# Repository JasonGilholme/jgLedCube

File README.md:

## jgLedCube

Open source software and hardware for creating an LED Cube.

### Software

The available code is intended to an SDK to allow people to make their cubes do more things as well as interact with other devices. 

The two main components of this are:

* core.cpp - intended for the cube micro controller and handles the data arrays for the cube.  It's implementation matches the provided hardware as well.
* serial.cpp - provides a standardized interface for communicating with an LED cube.  This provides higher level functions like set_led(), clear() etc to be used from Android Apps, Desktop programs and other micro controllers.

### Hardware

The hardware consists of two modular boards which are daisy chained together.  

The "column control board" acts as a base for the cube and provides 8 columns in a 4x2 arrangement.  This can be used to make arbitrary sized cubes, and shapes that aren't cubes too!

The "level control board" is used for multiplexing the different horizontal layers in the cube. It should be connected after all the column control boards.

A main controller and power solution is not provided as the requirements may vary depending on your exact product.  There are test programs for Arduino included, but it should also be possible to compile the core libs for other devices. STM32 etc.

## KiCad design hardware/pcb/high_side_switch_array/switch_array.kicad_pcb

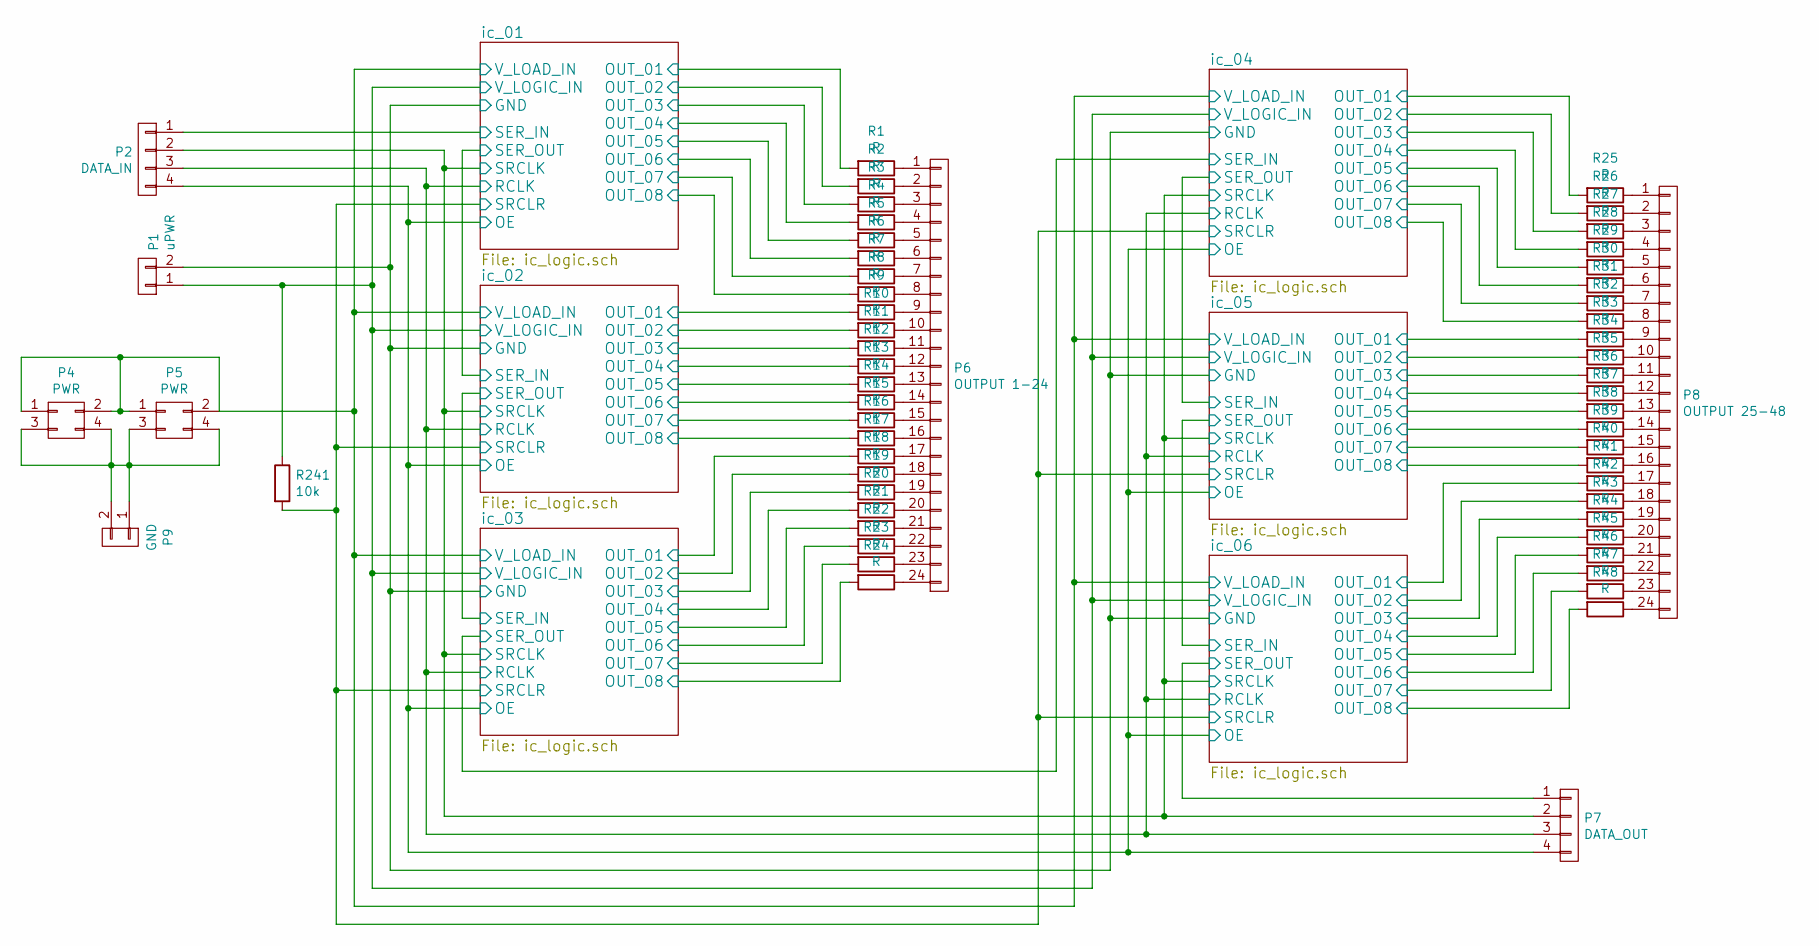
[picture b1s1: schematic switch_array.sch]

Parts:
P1: uPWR; Socket_Strip_Straight_1x02
P2: DATA_IN; Socket_Strip_Straight_1x04
P4, P5: PWR; Socket_Strip_Straight_2x02
P6: OUTPUT 1-24; Socket_Strip_Straight_2x12
P7: DATA_OUT; Socket_Strip_Straight_1x04
P8: OUTPUT 25-48; Socket_Strip_Straight_2x12
P9: GND; Socket_Strip_Straight_1x02
R1, R2, R3, R4, R5, R6, R7, R8, R9, R10, R11, R12, R13, R14, R15, R16, R17, R18, R19, R20, R21, R22, R23, R24, R25, R26, R27, R28, R29, R30, R31, R32, R33, R34, R35, R36, R37, R38, R39, R40, R41, R42, R43, R44, R45, R46, R47, R48: R; R_1206_HandSoldering
R241: 10k; R_1206_HandSoldering_NOREF

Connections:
/ic_01/OE: P2.4, P7.4; also elsewhere on the board
/ic_01/OUT_01: R1.2; also elsewhere on the board
/ic_01/OUT_02: R2.2; also elsewhere on the board
/ic_01/OUT_03: R3.2; also elsewhere on the board
/ic_01/OUT_04: R4.2; also elsewhere on the board
/ic_01/OUT_05: R5.2; also elsewhere on the board
/ic_01/OUT_06: R6.2; also elsewhere on the board
/ic_01/OUT_07: R7.2; also elsewhere on the board
/ic_01/OUT_08: R8.2; also elsewhere on the board
/ic_01/RCLK: P2.3, P7.3; also elsewhere on the board
/ic_01/SER_IN: P2.1; also elsewhere on the board
/ic_01/SRCLK: P2.2, P7.2; also elsewhere on the board
/ic_01/SRCLR: R241.2; also elsewhere on the board
/ic_01/V_LOAD_IN: P4.1, P4.2, P5.1, P5.2; also elsewhere on the board
/ic_02/OUT_01: R9.2; also elsewhere on the board
/ic_02/OUT_02: R10.2; also elsewhere on the board
/ic_02/OUT_03: R11.2; also elsewhere on the board
/ic_02/OUT_04: R12.2; also elsewhere on the board
/ic_02/OUT_05: R13.2; also elsewhere on the board
/ic_02/OUT_06: R14.2; also elsewhere on the board
/ic_02/OUT_07: R15.2; also elsewhere on the board
/ic_02/OUT_08: R16.2; also elsewhere on the board
/ic_03/OUT_01: R17.2; also elsewhere on the board
/ic_03/OUT_02: R18.2; also elsewhere on the board
/ic_03/OUT_03: R19.2; also elsewhere on the board
/ic_03/OUT_04: R20.2; also elsewhere on the board
/ic_03/OUT_05: R21.2; also elsewhere on the board
/ic_03/OUT_06: R22.2; also elsewhere on the board
/ic_03/OUT_07: R23.2; also elsewhere on the board
/ic_03/OUT_08: R24.2; also elsewhere on the board
/ic_04/OUT_01: R25.2; also elsewhere on the board
/ic_04/OUT_02: R26.2; also elsewhere on the board
/ic_04/OUT_03: R27.2; also elsewhere on the board
/ic_04/OUT_04: R28.2; also elsewhere on the board
/ic_04/OUT_05: R29.2; also elsewhere on the board
/ic_04/OUT_06: R30.2; also elsewhere on the board
/ic_04/OUT_07: R31.2; also elsewhere on the board
/ic_04/OUT_08: R32.2; also elsewhere on the board
/ic_05/OUT_01: R33.2; also elsewhere on the board
/ic_05/OUT_02: R34.2; also elsewhere on the board
/ic_05/OUT_03: R35.2; also elsewhere on the board
/ic_05/OUT_04: R36.2; also elsewhere on the board
/ic_05/OUT_05: R37.2; also elsewhere on the board
/ic_05/OUT_06: R38.2; also elsewhere on the board
/ic_05/OUT_07: R39.2; also elsewhere on the board
/ic_05/OUT_08: R40.2; also elsewhere on the board
/ic_06/OUT_01: R41.2; also elsewhere on the board
/ic_06/OUT_02: R42.2; also elsewhere on the board
/ic_06/OUT_03: R43.2; also elsewhere on the board
/ic_06/OUT_04: R44.2; also elsewhere on the board
/ic_06/OUT_05: R45.2; also elsewhere on the board
/ic_06/OUT_06: R46.2; also elsewhere on the board
/ic_06/OUT_07: R47.2; also elsewhere on the board
/ic_06/OUT_08: R48.2; also elsewhere on the board
/ic_06/SER_OUT: P7.1; also elsewhere on the board
GND: P1.2; also elsewhere on the board
unnamed: P4.3, P4.4, P5.3, P5.4, P9.1, P9.2
unnamed: P6.1, R1.1
unnamed: P6.2, R2.1
unnamed: P6.3, R3.1
unnamed: P6.4, R4.1
unnamed: P6.5, R5.1
unnamed: P6.6, R6.1
unnamed: P6.7, R7.1
unnamed: P6.8, R8.1
unnamed: P6.9, R9.1
unnamed: P6.10, R10.1
unnamed: P6.11, R11.1
unnamed: P6.12, R12.1
unnamed: P6.13, R13.1
unnamed: P6.14, R14.1
unnamed: P6.15, R15.1
unnamed: P6.16, R16.1
unnamed: P6.17, R17.1
unnamed: P6.18, R18.1
unnamed: P6.19, R19.1
unnamed: P6.20, R20.1
unnamed: P6.21, R21.1
unnamed: P6.22, R22.1
unnamed: P6.23, R23.1
unnamed: P6.24, R24.1
unnamed: P8.1, R25.1
unnamed: P8.2, R26.1
unnamed: P8.3, R27.1
unnamed: P8.4, R28.1
unnamed: P8.5, R29.1
unnamed: P8.6, R30.1
unnamed: P8.7, R31.1
unnamed: P8.8, R32.1
unnamed: P8.9, R33.1
unnamed: P8.10, R34.1
unnamed: P8.11, R35.1
unnamed: P8.12, R36.1
unnamed: P8.13, R37.1
unnamed: P8.14, R38.1
unnamed: P8.15, R39.1
unnamed: P8.16, R40.1
unnamed: P8.17, R41.1
unnamed: P8.18, R42.1
unnamed: P8.19, R43.1
unnamed: P8.20, R44.1
unnamed: P8.21, R45.1
unnamed: P8.22, R46.1
unnamed: P8.23, R47.1
unnamed: P8.24, R48.1
VCC: P1.1, R241.1; also elsewhere on the board

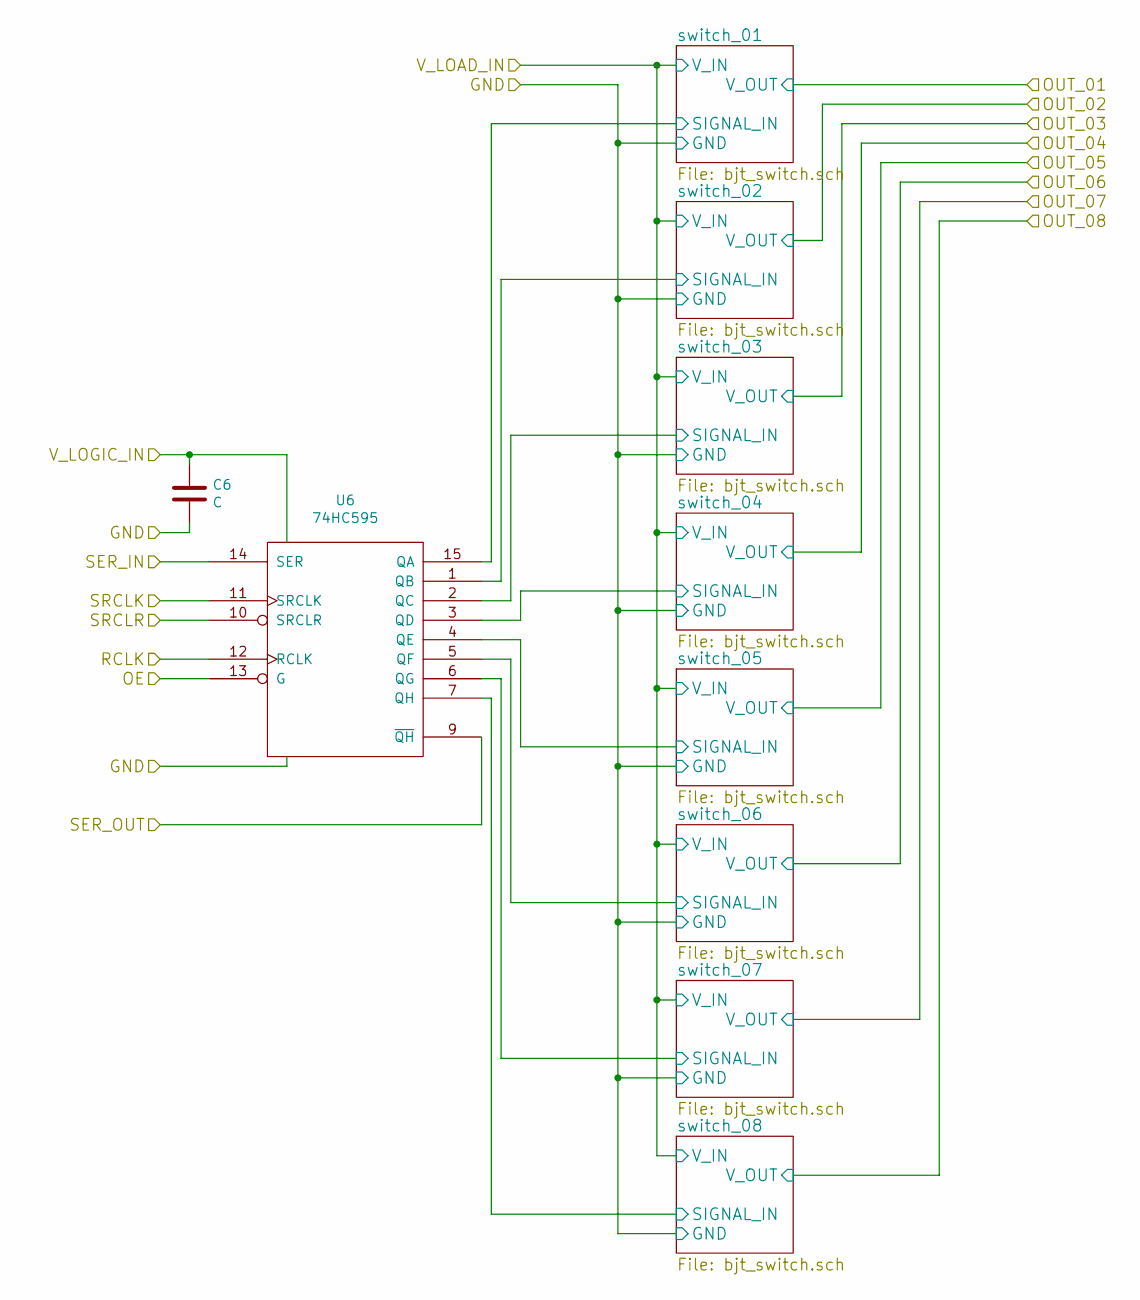
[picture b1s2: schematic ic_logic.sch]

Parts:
C1: C; C_1206_HandSoldering
U1: 74HC595; SO-16-N

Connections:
/ic_01/OE: U1.13 (G); also elsewhere on the board
/ic_01/RCLK: U1.12 (RCLK); also elsewhere on the board
/ic_01/SER_IN: U1.14 (SER); also elsewhere on the board
/ic_01/SRCLK: U1.11 (SRCLK); also elsewhere on the board
/ic_01/SRCLR: U1.10 (SRCLR); also elsewhere on the board
/ic_01/switch_01/SIGNAL_IN: U1.15 (QA); also elsewhere on the board
/ic_01/switch_02/SIGNAL_IN: U1.1 (QB); also elsewhere on the board
/ic_01/switch_03/SIGNAL_IN: U1.2 (QC); also elsewhere on the board
/ic_01/switch_04/SIGNAL_IN: U1.3 (QD); also elsewhere on the board
/ic_01/switch_05/SIGNAL_IN: U1.4 (QE); also elsewhere on the board
/ic_01/switch_06/SIGNAL_IN: U1.5 (QF); also elsewhere on the board
/ic_01/switch_07/SIGNAL_IN: U1.6 (QG); also elsewhere on the board
/ic_01/switch_08/SIGNAL_IN: U1.7 (QH); also elsewhere on the board
/ic_02/SER_IN: U1.9 (~QH); also elsewhere on the board
GND: C1.2, U1.8 (GND); also elsewhere on the board
VCC: C1.1, U1.16 (VCC); also elsewhere on the board

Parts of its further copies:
C2, C3, C4, C5, C6: C; C_1206_HandSoldering
U2, U3, U4, U5, U6: 74HC595; SO-16-N

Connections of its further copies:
/ic_01/OE: U2.13 (G), U3.13 (G), U4.13 (G), U5.13 (G), U6.13 (G); also elsewhere on the board
/ic_01/RCLK: U2.12 (RCLK), U3.12 (RCLK), U4.12 (RCLK), U5.12 (RCLK), U6.12 (RCLK); also elsewhere on the board
/ic_01/SRCLK: U2.11 (SRCLK), U3.11 (SRCLK), U4.11 (SRCLK), U5.11 (SRCLK), U6.11 (SRCLK); also elsewhere on the board
/ic_01/SRCLR: U2.10 (SRCLR), U3.10 (SRCLR), U4.10 (SRCLR), U5.10 (SRCLR), U6.10 (SRCLR); also elsewhere on the board
/ic_02/SER_IN: U2.14 (SER); also elsewhere on the board
/ic_02/switch_01/SIGNAL_IN: U2.15 (QA); also elsewhere on the board
/ic_02/switch_02/SIGNAL_IN: U2.1 (QB); also elsewhere on the board
/ic_02/switch_03/SIGNAL_IN: U2.2 (QC); also elsewhere on the board
/ic_02/switch_04/SIGNAL_IN: U2.3 (QD); also elsewhere on the board
/ic_02/switch_05/SIGNAL_IN: U2.4 (QE); also elsewhere on the board
/ic_02/switch_06/SIGNAL_IN: U2.5 (QF); also elsewhere on the board
/ic_02/switch_07/SIGNAL_IN: U2.6 (QG); also elsewhere on the board
/ic_02/switch_08/SIGNAL_IN: U2.7 (QH); also elsewhere on the board
/ic_03/SER_IN: U2.9 (~QH), U3.14 (SER)
/ic_03/switch_01/SIGNAL_IN: U3.15 (QA); also elsewhere on the board
/ic_03/switch_02/SIGNAL_IN: U3.1 (QB); also elsewhere on the board
/ic_03/switch_03/SIGNAL_IN: U3.2 (QC); also elsewhere on the board
/ic_03/switch_04/SIGNAL_IN: U3.3 (QD); also elsewhere on the board
/ic_03/switch_05/SIGNAL_IN: U3.4 (QE); also elsewhere on the board
/ic_03/switch_06/SIGNAL_IN: U3.5 (QF); also elsewhere on the board
/ic_03/switch_07/SIGNAL_IN: U3.6 (QG); also elsewhere on the board
/ic_03/switch_08/SIGNAL_IN: U3.7 (QH); also elsewhere on the board
/ic_04/SER_IN: U3.9 (~QH), U4.14 (SER)
/ic_04/switch_01/SIGNAL_IN: U4.15 (QA); also elsewhere on the board
/ic_04/switch_02/SIGNAL_IN: U4.1 (QB); also elsewhere on the board
/ic_04/switch_03/SIGNAL_IN: U4.2 (QC); also elsewhere on the board
/ic_04/switch_04/SIGNAL_IN: U4.3 (QD); also elsewhere on the board
/ic_04/switch_05/SIGNAL_IN: U4.4 (QE); also elsewhere on the board
/ic_04/switch_06/SIGNAL_IN: U4.5 (QF); also elsewhere on the board
/ic_04/switch_07/SIGNAL_IN: U4.6 (QG); also elsewhere on the board
/ic_04/switch_08/SIGNAL_IN: U4.7 (QH); also elsewhere on the board
/ic_05/SER_IN: U4.9 (~QH), U5.14 (SER)
/ic_05/switch_01/SIGNAL_IN: U5.15 (QA); also elsewhere on the board
/ic_05/switch_02/SIGNAL_IN: U5.1 (QB); also elsewhere on the board
/ic_05/switch_03/SIGNAL_IN: U5.2 (QC); also elsewhere on the board
/ic_05/switch_04/SIGNAL_IN: U5.3 (QD); also elsewhere on the board
/ic_05/switch_05/SIGNAL_IN: U5.4 (QE); also elsewhere on the board
/ic_05/switch_06/SIGNAL_IN: U5.5 (QF); also elsewhere on the board
/ic_05/switch_07/SIGNAL_IN: U5.6 (QG); also elsewhere on the board
/ic_05/switch_08/SIGNAL_IN: U5.7 (QH); also elsewhere on the board
/ic_06/SER_IN: U5.9 (~QH), U6.14 (SER)
/ic_06/SER_OUT: U6.9 (~QH); also elsewhere on the board
/ic_06/switch_01/SIGNAL_IN: U6.15 (QA); also elsewhere on the board
/ic_06/switch_02/SIGNAL_IN: U6.1 (QB); also elsewhere on the board
/ic_06/switch_03/SIGNAL_IN: U6.2 (QC); also elsewhere on the board
/ic_06/switch_04/SIGNAL_IN: U6.3 (QD); also elsewhere on the board
/ic_06/switch_05/SIGNAL_IN: U6.4 (QE); also elsewhere on the board
/ic_06/switch_06/SIGNAL_IN: U6.5 (QF); also elsewhere on the board
/ic_06/switch_07/SIGNAL_IN: U6.6 (QG); also elsewhere on the board
/ic_06/switch_08/SIGNAL_IN: U6.7 (QH); also elsewhere on the board
GND: C2.2, C3.2, C4.2, C5.2, C6.2, U2.8 (GND), U3.8 (GND), U4.8 (GND), U5.8 (GND), U6.8 (GND); also elsewhere on the board
VCC: C2.1, C3.1, C4.1, C5.1, C6.1, U2.16 (VCC), U3.16 (VCC), U4.16 (VCC), U5.16 (VCC), U6.16 (VCC); also elsewhere on the board

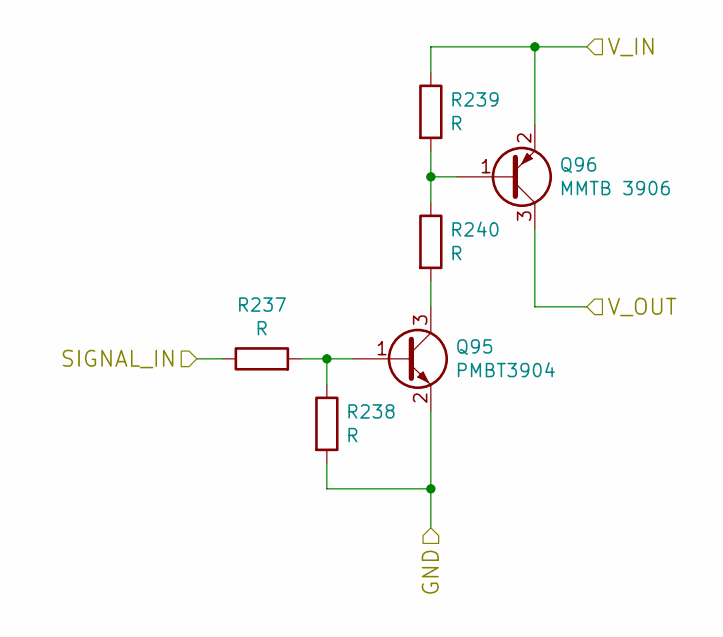
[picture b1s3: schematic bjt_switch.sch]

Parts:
Q1: PMBT3904; SOT-23
Q2: MMTB 3906; SOT-23
R49, R50, R51, R52: R; R_1206_HandSoldering

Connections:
/ic_01/OUT_02: Q2.3 (C); also elsewhere on the board
/ic_01/V_LOAD_IN: Q2.2 (E), R51.1; also elsewhere on the board
/ic_01/switch_02/SIGNAL_IN: R49.1; also elsewhere on the board
GND: Q1.2 (E), R50.2; also elsewhere on the board
unnamed: Q1.1 (B), R49.2, R50.1
unnamed: Q1.3 (C), R52.2
unnamed: Q2.1 (B), R51.2, R52.1

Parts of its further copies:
Q3, Q5, Q7, Q9, Q11, Q13, Q15, Q17, Q19, Q21, Q23, Q25, Q27, Q29, Q31, Q33, Q35, Q37, Q39, Q41, Q43, Q45, Q47, Q49, Q51, Q53, Q55, Q57, Q59, Q61, Q63, Q65, Q67, Q69, Q71, Q73, Q75, Q77, Q79, Q81, Q83, Q85, Q87, Q89, Q91, Q93, Q95: PMBT3904; SOT-23
Q4, Q6, Q8, Q10, Q12, Q14, Q16, Q18, Q20, Q22, Q24, Q26, Q28, Q30, Q32, Q34, Q36, Q38, Q40, Q42, Q44, Q46, Q48, Q50, Q52, Q54, Q56, Q58, Q60, Q62, Q64, Q66, Q68, Q70, Q72, Q74, Q76, Q78, Q80, Q82, Q84, Q86, Q88, Q90, Q92, Q94, Q96: MMTB 3906; SOT-23
R53, R54, R55, R56, R57, R58, R59, R60, R61, R62, R63, R64, R65, R66, R67, R68, R69, R70, R71, R72, R73, R74, R75, R76, R77, R78, R79, R80, R81, R82, R83, R84, R85, R86, R87, R88, R89, R90, R91, R92, R93, R94, R95, R96, R97, R98, R99, R100, R101, R102, R103, R104, R105, R106, R107, R108, R109, R110, R111, R112, R113, R114, R115, R116, R117, R118, R119, R120, R121, R122, R123, R124, R125, R126, R127, R128, R129, R130, R131, R132, R133, R134, R135, R136, R137, R138, R139, R140, R141, R142, R143, R144, R145, R146, R147, R148, R149, R150, R151, R152, R153, R154, R155, R156, R157, R158, R159, R160, R161, R162, R163, R164, R165, R166, R167, R168, R169, R170, R171, R172, R173, R174, R175, R176, R177, R178, R179, R180, R181, R182, R183, R184, R185, R186, R187, R188, R189, R190, R191, R192, R193, R194, R195, R196, R197, R198, R199, R200, R201, R202, R203, R204, R205, R206, R207, R208, R209, R210, R211, R212, R213, R214, R215, R216, R217, R218, R219, R220, R221, R222, R223, R224, R225, R226, R227, R228, R229, R230, R231, R232, R233, R234, R235, R236, R237, R238, R239, R240: R; R_1206_HandSoldering

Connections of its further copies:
/ic_01/OUT_01: Q16.3 (C); also elsewhere on the board
/ic_01/OUT_03: Q4.3 (C); also elsewhere on the board
/ic_01/OUT_04: Q6.3 (C); also elsewhere on the board
/ic_01/OUT_05: Q8.3 (C); also elsewhere on the board
/ic_01/OUT_06: Q10.3 (C); also elsewhere on the board
/ic_01/OUT_07: Q12.3 (C); also elsewhere on the board
/ic_01/OUT_08: Q14.3 (C); also elsewhere on the board
/ic_01/V_LOAD_IN: Q4.2 (E), Q6.2 (E), Q8.2 (E), Q10.2 (E), Q12.2 (E), Q14.2 (E), Q16.2 (E), Q18.2 (E), Q20.2 (E), Q22.2 (E), Q24.2 (E), Q26.2 (E), Q28.2 (E), Q30.2 (E), Q32.2 (E), Q34.2 (E), Q36.2 (E), Q38.2 (E), Q40.2 (E), Q42.2 (E), Q44.2 (E), Q46.2 (E), Q48.2 (E), Q50.2 (E), Q52.2 (E), Q54.2 (E), Q56.2 (E), Q58.2 (E), Q60.2 (E), Q62.2 (E), Q64.2 (E), Q66.2 (E), Q68.2 (E), Q70.2 (E), Q72.2 (E), Q74.2 (E), Q76.2 (E), Q78.2 (E), Q80.2 (E), Q82.2 (E), Q84.2 (E), Q86.2 (E), Q88.2 (E), Q90.2 (E), Q92.2 (E), Q94.2 (E), Q96.2 (E), R55.1, R59.1, R63.1, R67.1, R71.1, R75.1, R79.1, R83.1, R87.1, R91.1, R95.1, R99.1, R103.1, R107.1, R111.1, R115.1, R119.1, R123.1, R127.1, R131.1, R135.1, R139.1, R143.1, R147.1, R151.1, R155.1, R159.1, R163.1, R167.1, R171.1, R175.1, R179.1, R183.1, R187.1, R191.1, R195.1, R199.1, R203.1, R207.1, R211.1, R215.1, R219.1, R223.1, R227.1, R231.1, R235.1, R239.1; also elsewhere on the board
/ic_01/switch_01/SIGNAL_IN: R77.1; also elsewhere on the board
/ic_01/switch_03/SIGNAL_IN: R53.1; also elsewhere on the board
/ic_01/switch_04/SIGNAL_IN: R57.1; also elsewhere on the board
/ic_01/switch_05/SIGNAL_IN: R61.1; also elsewhere on the board
/ic_01/switch_06/SIGNAL_IN: R65.1; also elsewhere on the board
/ic_01/switch_07/SIGNAL_IN: R69.1; also elsewhere on the board
/ic_01/switch_08/SIGNAL_IN: R73.1; also elsewhere on the board
/ic_02/OUT_01: Q32.3 (C); also elsewhere on the board
/ic_02/OUT_02: Q18.3 (C); also elsewhere on the board
/ic_02/OUT_03: Q20.3 (C); also elsewhere on the board
/ic_02/OUT_04: Q22.3 (C); also elsewhere on the board
/ic_02/OUT_05: Q24.3 (C); also elsewhere on the board
/ic_02/OUT_06: Q26.3 (C); also elsewhere on the board
/ic_02/OUT_07: Q28.3 (C); also elsewhere on the board
/ic_02/OUT_08: Q30.3 (C); also elsewhere on the board
/ic_02/switch_01/SIGNAL_IN: R109.1; also elsewhere on the board
/ic_02/switch_02/SIGNAL_IN: R81.1; also elsewhere on the board
/ic_02/switch_03/SIGNAL_IN: R85.1; also elsewhere on the board
/ic_02/switch_04/SIGNAL_IN: R89.1; also elsewhere on the board
/ic_02/switch_05/SIGNAL_IN: R93.1; also elsewhere on the board
/ic_02/switch_06/SIGNAL_IN: R97.1; also elsewhere on the board
/ic_02/switch_07/SIGNAL_IN: R101.1; also elsewhere on the board
/ic_02/switch_08/SIGNAL_IN: R105.1; also elsewhere on the board
/ic_03/OUT_01: Q48.3 (C); also elsewhere on the board
/ic_03/OUT_02: Q34.3 (C); also elsewhere on the board
/ic_03/OUT_03: Q36.3 (C); also elsewhere on the board
/ic_03/OUT_04: Q38.3 (C); also elsewhere on the board
/ic_03/OUT_05: Q40.3 (C); also elsewhere on the board
/ic_03/OUT_06: Q42.3 (C); also elsewhere on the board
/ic_03/OUT_07: Q44.3 (C); also elsewhere on the board
/ic_03/OUT_08: Q46.3 (C); also elsewhere on the board
/ic_03/switch_01/SIGNAL_IN: R141.1; also elsewhere on the board
/ic_03/switch_02/SIGNAL_IN: R113.1; also elsewhere on the board
/ic_03/switch_03/SIGNAL_IN: R117.1; also elsewhere on the board
/ic_03/switch_04/SIGNAL_IN: R121.1; also elsewhere on the board
/ic_03/switch_05/SIGNAL_IN: R125.1; also elsewhere on the board
/ic_03/switch_06/SIGNAL_IN: R129.1; also elsewhere on the board
/ic_03/switch_07/SIGNAL_IN: R133.1; also elsewhere on the board
/ic_03/switch_08/SIGNAL_IN: R137.1; also elsewhere on the board
/ic_04/OUT_01: Q64.3 (C); also elsewhere on the board
/ic_04/OUT_02: Q50.3 (C); also elsewhere on the board
/ic_04/OUT_03: Q52.3 (C); also elsewhere on the board
/ic_04/OUT_04: Q54.3 (C); also elsewhere on the board
/ic_04/OUT_05: Q56.3 (C); also elsewhere on the board
/ic_04/OUT_06: Q58.3 (C); also elsewhere on the board
/ic_04/OUT_07: Q60.3 (C); also elsewhere on the board
/ic_04/OUT_08: Q62.3 (C); also elsewhere on the board
/ic_04/switch_01/SIGNAL_IN: R173.1; also elsewhere on the board
/ic_04/switch_02/SIGNAL_IN: R145.1; also elsewhere on the board
/ic_04/switch_03/SIGNAL_IN: R149.1; also elsewhere on the board
/ic_04/switch_04/SIGNAL_IN: R153.1; also elsewhere on the board
/ic_04/switch_05/SIGNAL_IN: R157.1; also elsewhere on the board
/ic_04/switch_06/SIGNAL_IN: R161.1; also elsewhere on the board
/ic_04/switch_07/SIGNAL_IN: R165.1; also elsewhere on the board
/ic_04/switch_08/SIGNAL_IN: R169.1; also elsewhere on the board
/ic_05/OUT_01: Q80.3 (C); also elsewhere on the board
/ic_05/OUT_02: Q66.3 (C); also elsewhere on the board
/ic_05/OUT_03: Q68.3 (C); also elsewhere on the board
/ic_05/OUT_04: Q70.3 (C); also elsewhere on the board
/ic_05/OUT_05: Q72.3 (C); also elsewhere on the board
/ic_05/OUT_06: Q74.3 (C); also elsewhere on the board
/ic_05/OUT_07: Q76.3 (C); also elsewhere on the board
/ic_05/OUT_08: Q78.3 (C); also elsewhere on the board
/ic_05/switch_01/SIGNAL_IN: R205.1; also elsewhere on the board
/ic_05/switch_02/SIGNAL_IN: R177.1; also elsewhere on the board
/ic_05/switch_03/SIGNAL_IN: R181.1; also elsewhere on the board
/ic_05/switch_04/SIGNAL_IN: R185.1; also elsewhere on the board
/ic_05/switch_05/SIGNAL_IN: R189.1; also elsewhere on the board
/ic_05/switch_06/SIGNAL_IN: R193.1; also elsewhere on the board
/ic_05/switch_07/SIGNAL_IN: R197.1; also elsewhere on the board
/ic_05/switch_08/SIGNAL_IN: R201.1; also elsewhere on the board
/ic_06/OUT_01: Q96.3 (C); also elsewhere on the board
/ic_06/OUT_02: Q82.3 (C); also elsewhere on the board
/ic_06/OUT_03: Q84.3 (C); also elsewhere on the board
/ic_06/OUT_04: Q86.3 (C); also elsewhere on the board
/ic_06/OUT_05: Q88.3 (C); also elsewhere on the board
/ic_06/OUT_06: Q90.3 (C); also elsewhere on the board
/ic_06/OUT_07: Q92.3 (C); also elsewhere on the board
/ic_06/OUT_08: Q94.3 (C); also elsewhere on the board
/ic_06/switch_01/SIGNAL_IN: R237.1; also elsewhere on the board
/ic_06/switch_02/SIGNAL_IN: R209.1; also elsewhere on the board
/ic_06/switch_03/SIGNAL_IN: R213.1; also elsewhere on the board
/ic_06/switch_04/SIGNAL_IN: R217.1; also elsewhere on the board
/ic_06/switch_05/SIGNAL_IN: R221.1; also elsewhere on the board
/ic_06/switch_06/SIGNAL_IN: R225.1; also elsewhere on the board
/ic_06/switch_07/SIGNAL_IN: R229.1; also elsewhere on the board
/ic_06/switch_08/SIGNAL_IN: R233.1; also elsewhere on the board
GND: Q3.2 (E), Q5.2 (E), Q7.2 (E), Q9.2 (E), Q11.2 (E), Q13.2 (E), Q15.2 (E), Q17.2 (E), Q19.2 (E), Q21.2 (E), Q23.2 (E), Q25.2 (E), Q27.2 (E), Q29.2 (E), Q31.2 (E), Q33.2 (E), Q35.2 (E), Q37.2 (E), Q39.2 (E), Q41.2 (E), Q43.2 (E), Q45.2 (E), Q47.2 (E), Q49.2 (E), Q51.2 (E), Q53.2 (E), Q55.2 (E), Q57.2 (E), Q59.2 (E), Q61.2 (E), Q63.2 (E), Q65.2 (E), Q67.2 (E), Q69.2 (E), Q71.2 (E), Q73.2 (E), Q75.2 (E), Q77.2 (E), Q79.2 (E), Q81.2 (E), Q83.2 (E), Q85.2 (E), Q87.2 (E), Q89.2 (E), Q91.2 (E), Q93.2 (E), Q95.2 (E), R54.2, R58.2, R62.2, R66.2, R70.2, R74.2, R78.2, R82.2, R86.2, R90.2, R94.2, R98.2, R102.2, R106.2, R110.2, R114.2, R118.2, R122.2, R126.2, R130.2, R134.2, R138.2, R142.2, R146.2, R150.2, R154.2, R158.2, R162.2, R166.2, R170.2, R174.2, R178.2, R182.2, R186.2, R190.2, R194.2, R198.2, R202.2, R206.2, R210.2, R214.2, R218.2, R222.2, R226.2, R230.2, R234.2, R238.2; also elsewhere on the board
unnamed: Q3.1 (B), R53.2, R54.1
unnamed: Q3.3 (C), R56.2
unnamed: Q4.1 (B), R55.2, R56.1
unnamed: Q5.1 (B), R57.2, R58.1
unnamed: Q5.3 (C), R60.2
unnamed: Q6.1 (B), R59.2, R60.1
unnamed: Q7.1 (B), R61.2, R62.1
unnamed: Q7.3 (C), R64.2
unnamed: Q8.1 (B), R63.2, R64.1
unnamed: Q9.1 (B), R65.2, R66.1
unnamed: Q9.3 (C), R68.2
unnamed: Q10.1 (B), R67.2, R68.1
unnamed: Q11.1 (B), R69.2, R70.1
unnamed: Q11.3 (C), R72.2
unnamed: Q12.1 (B), R71.2, R72.1
unnamed: Q13.1 (B), R73.2, R74.1
unnamed: Q13.3 (C), R76.2
unnamed: Q14.1 (B), R75.2, R76.1
unnamed: Q15.1 (B), R77.2, R78.1
unnamed: Q15.3 (C), R80.2
unnamed: Q16.1 (B), R79.2, R80.1
unnamed: Q17.1 (B), R81.2, R82.1
unnamed: Q17.3 (C), R84.2
unnamed: Q18.1 (B), R83.2, R84.1
unnamed: Q19.1 (B), R85.2, R86.1
unnamed: Q19.3 (C), R88.2
unnamed: Q20.1 (B), R87.2, R88.1
unnamed: Q21.1 (B), R89.2, R90.1
unnamed: Q21.3 (C), R92.2
unnamed: Q22.1 (B), R91.2, R92.1
unnamed: Q23.1 (B), R93.2, R94.1
unnamed: Q23.3 (C), R96.2
unnamed: Q24.1 (B), R95.2, R96.1
unnamed: Q25.1 (B), R97.2, R98.1
unnamed: Q25.3 (C), R100.2
unnamed: Q26.1 (B), R99.2, R100.1
unnamed: Q27.1 (B), R101.2, R102.1
unnamed: Q27.3 (C), R104.2
unnamed: Q28.1 (B), R103.2, R104.1
unnamed: Q29.1 (B), R105.2, R106.1
unnamed: Q29.3 (C), R108.2
unnamed: Q30.1 (B), R107.2, R108.1
unnamed: Q31.1 (B), R109.2, R110.1
unnamed: Q31.3 (C), R112.2
unnamed: Q32.1 (B), R111.2, R112.1
unnamed: Q33.1 (B), R113.2, R114.1
unnamed: Q33.3 (C), R116.2
unnamed: Q34.1 (B), R115.2, R116.1
unnamed: Q35.1 (B), R117.2, R118.1
unnamed: Q35.3 (C), R120.2
unnamed: Q36.1 (B), R119.2, R120.1
unnamed: Q37.1 (B), R121.2, R122.1
unnamed: Q37.3 (C), R124.2
unnamed: Q38.1 (B), R123.2, R124.1
unnamed: Q39.1 (B), R125.2, R126.1
unnamed: Q39.3 (C), R128.2
unnamed: Q40.1 (B), R127.2, R128.1
unnamed: Q41.1 (B), R129.2, R130.1
unnamed: Q41.3 (C), R132.2
unnamed: Q42.1 (B), R131.2, R132.1
unnamed: Q43.1 (B), R133.2, R134.1
unnamed: Q43.3 (C), R136.2
unnamed: Q44.1 (B), R135.2, R136.1
unnamed: Q45.1 (B), R137.2, R138.1
unnamed: Q45.3 (C), R140.2
unnamed: Q46.1 (B), R139.2, R140.1
unnamed: Q47.1 (B), R141.2, R142.1
unnamed: Q47.3 (C), R144.2
unnamed: Q48.1 (B), R143.2, R144.1
unnamed: Q49.1 (B), R145.2, R146.1
unnamed: Q49.3 (C), R148.2
unnamed: Q50.1 (B), R147.2, R148.1
unnamed: Q51.1 (B), R149.2, R150.1
unnamed: Q51.3 (C), R152.2
unnamed: Q52.1 (B), R151.2, R152.1
unnamed: Q53.1 (B), R153.2, R154.1
unnamed: Q53.3 (C), R156.2
unnamed: Q54.1 (B), R155.2, R156.1
unnamed: Q55.1 (B), R157.2, R158.1
unnamed: Q55.3 (C), R160.2
unnamed: Q56.1 (B), R159.2, R160.1
unnamed: Q57.1 (B), R161.2, R162.1
unnamed: Q57.3 (C), R164.2
unnamed: Q58.1 (B), R163.2, R164.1
unnamed: Q59.1 (B), R165.2, R166.1
unnamed: Q59.3 (C), R168.2
unnamed: Q60.1 (B), R167.2, R168.1
unnamed: Q61.1 (B), R169.2, R170.1
unnamed: Q61.3 (C), R172.2
unnamed: Q62.1 (B), R171.2, R172.1
unnamed: Q63.1 (B), R173.2, R174.1
unnamed: Q63.3 (C), R176.2
unnamed: Q64.1 (B), R175.2, R176.1
unnamed: Q65.1 (B), R177.2, R178.1
unnamed: Q65.3 (C), R180.2
unnamed: Q66.1 (B), R179.2, R180.1
unnamed: Q67.1 (B), R181.2, R182.1
unnamed: Q67.3 (C), R184.2
unnamed: Q68.1 (B), R183.2, R184.1
unnamed: Q69.1 (B), R185.2, R186.1
unnamed: Q69.3 (C), R188.2
unnamed: Q70.1 (B), R187.2, R188.1
unnamed: Q71.1 (B), R189.2, R190.1
unnamed: Q71.3 (C), R192.2
unnamed: Q72.1 (B), R191.2, R192.1
unnamed: Q73.1 (B), R193.2, R194.1
unnamed: Q73.3 (C), R196.2
unnamed: Q74.1 (B), R195.2, R196.1
unnamed: Q75.1 (B), R197.2, R198.1
unnamed: Q75.3 (C), R200.2
unnamed: Q76.1 (B), R199.2, R200.1
unnamed: Q77.1 (B), R201.2, R202.1
unnamed: Q77.3 (C), R204.2
unnamed: Q78.1 (B), R203.2, R204.1
unnamed: Q79.1 (B), R205.2, R206.1
unnamed: Q79.3 (C), R208.2
unnamed: Q80.1 (B), R207.2, R208.1
unnamed: Q81.1 (B), R209.2, R210.1
unnamed: Q81.3 (C), R212.2
unnamed: Q82.1 (B), R211.2, R212.1
unnamed: Q83.1 (B), R213.2, R214.1
unnamed: Q83.3 (C), R216.2
unnamed: Q84.1 (B), R215.2, R216.1
unnamed: Q85.1 (B), R217.2, R218.1
unnamed: Q85.3 (C), R220.2
unnamed: Q86.1 (B), R219.2, R220.1
unnamed: Q87.1 (B), R221.2, R222.1
unnamed: Q87.3 (C), R224.2
unnamed: Q88.1 (B), R223.2, R224.1
unnamed: Q89.1 (B), R225.2, R226.1
unnamed: Q89.3 (C), R228.2
unnamed: Q90.1 (B), R227.2, R228.1
unnamed: Q91.1 (B), R229.2, R230.1
unnamed: Q91.3 (C), R232.2
unnamed: Q92.1 (B), R231.2, R232.1
unnamed: Q93.1 (B), R233.2, R234.1
unnamed: Q93.3 (C), R236.2
unnamed: Q94.1 (B), R235.2, R236.1
unnamed: Q95.1 (B), R237.2, R238.1
unnamed: Q95.3 (C), R240.2
unnamed: Q96.1 (B), R239.2, R240.1

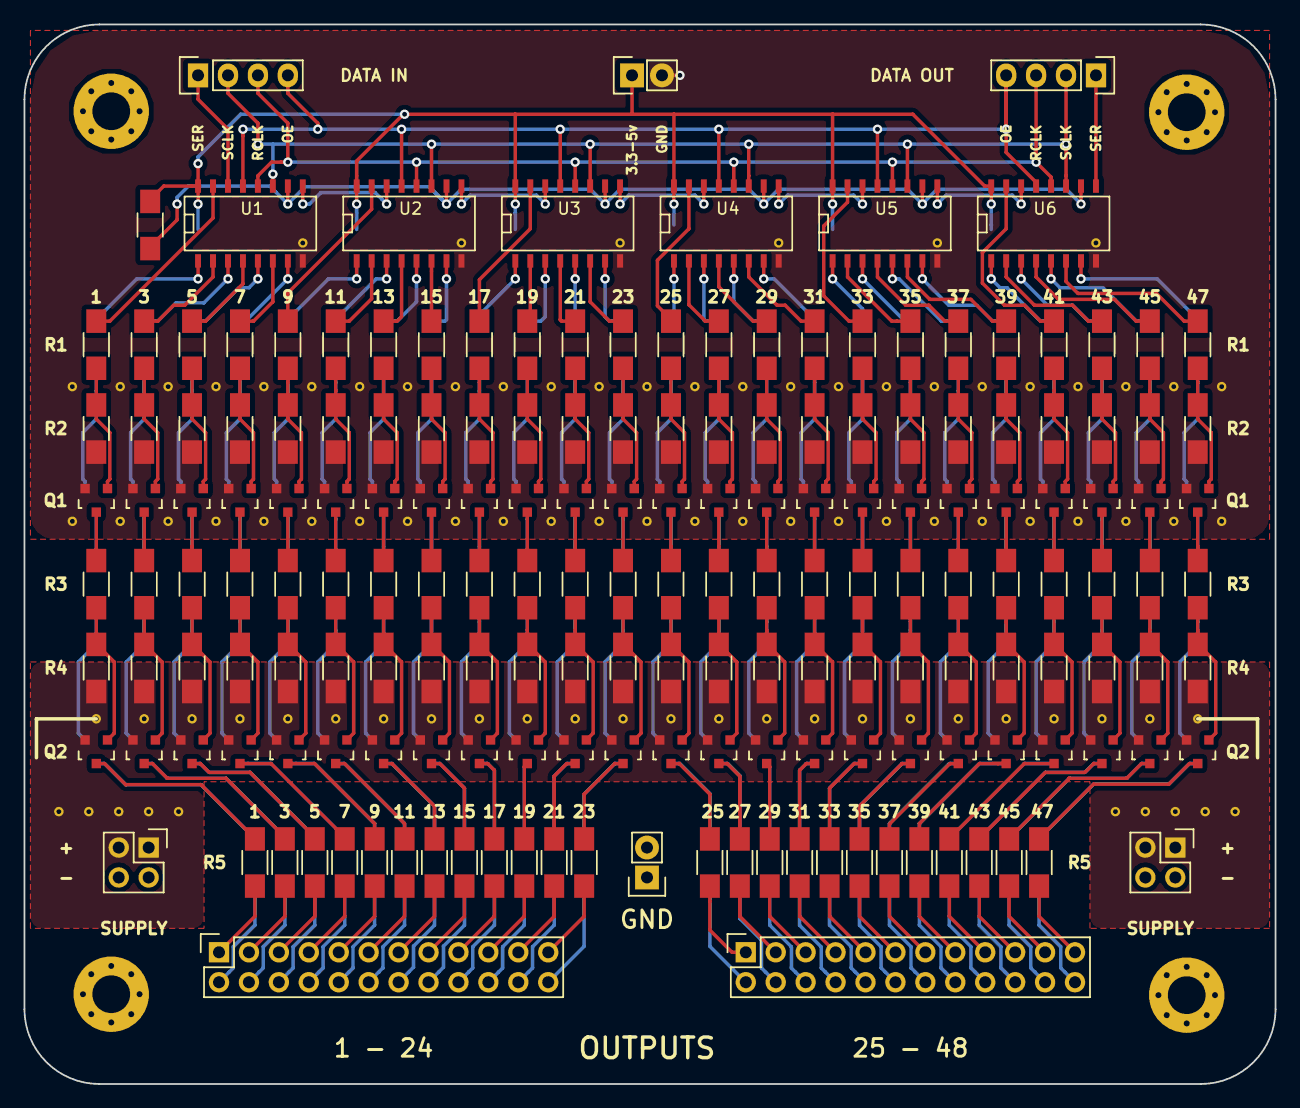
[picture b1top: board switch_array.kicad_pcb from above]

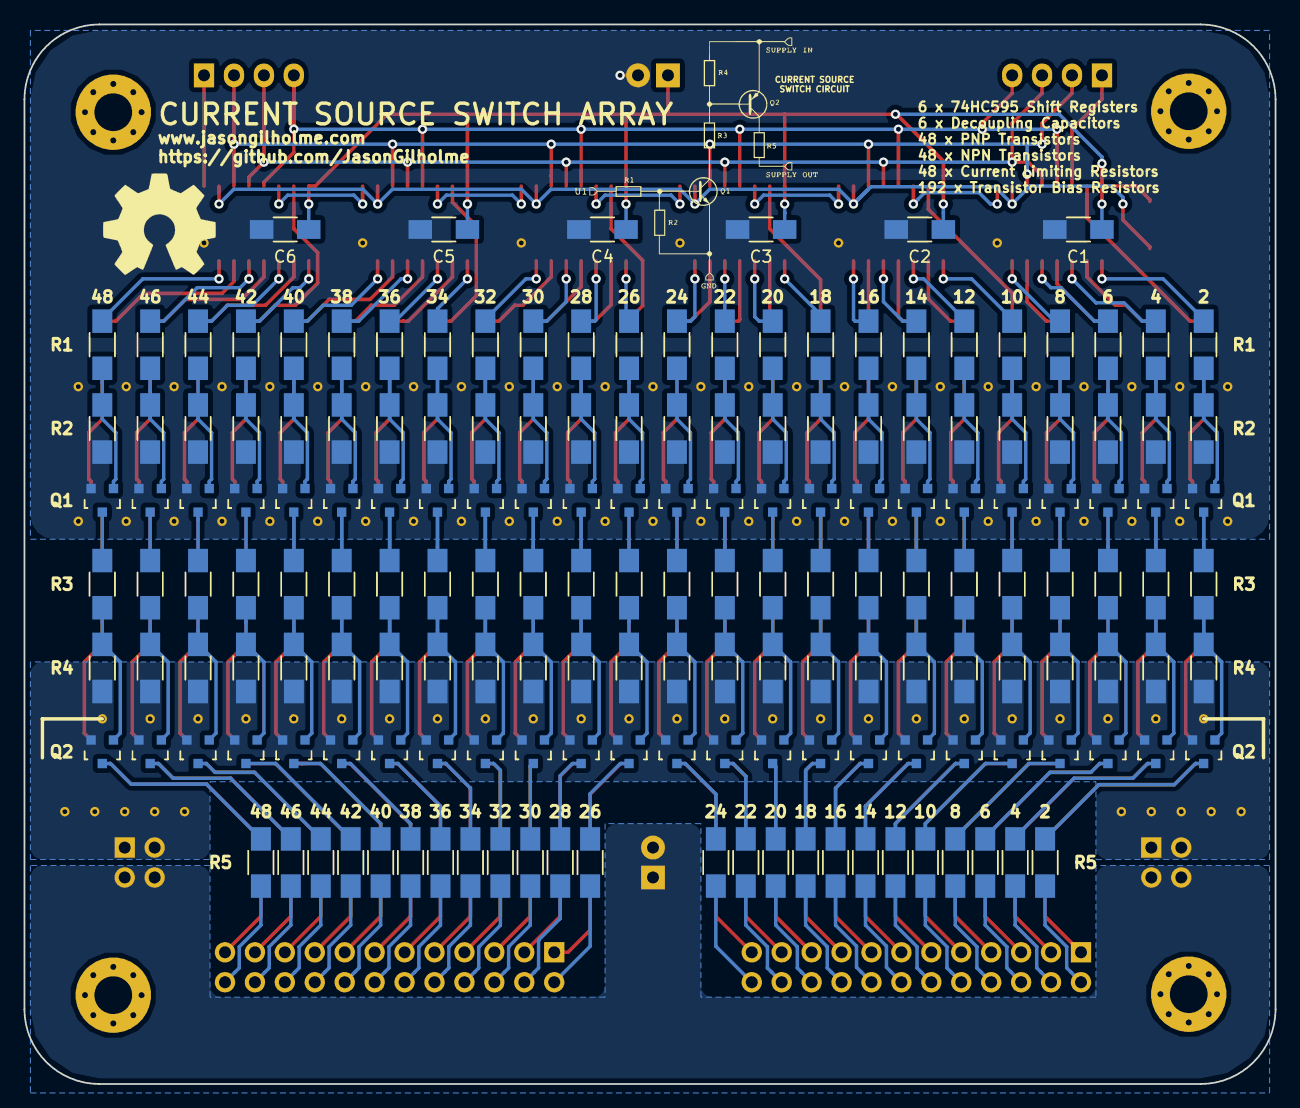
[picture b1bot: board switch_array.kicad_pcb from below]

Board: 2 copper layers, 106.2 x 89.9 mm, 357 parts (174 on the bottom side), 303 nets.
